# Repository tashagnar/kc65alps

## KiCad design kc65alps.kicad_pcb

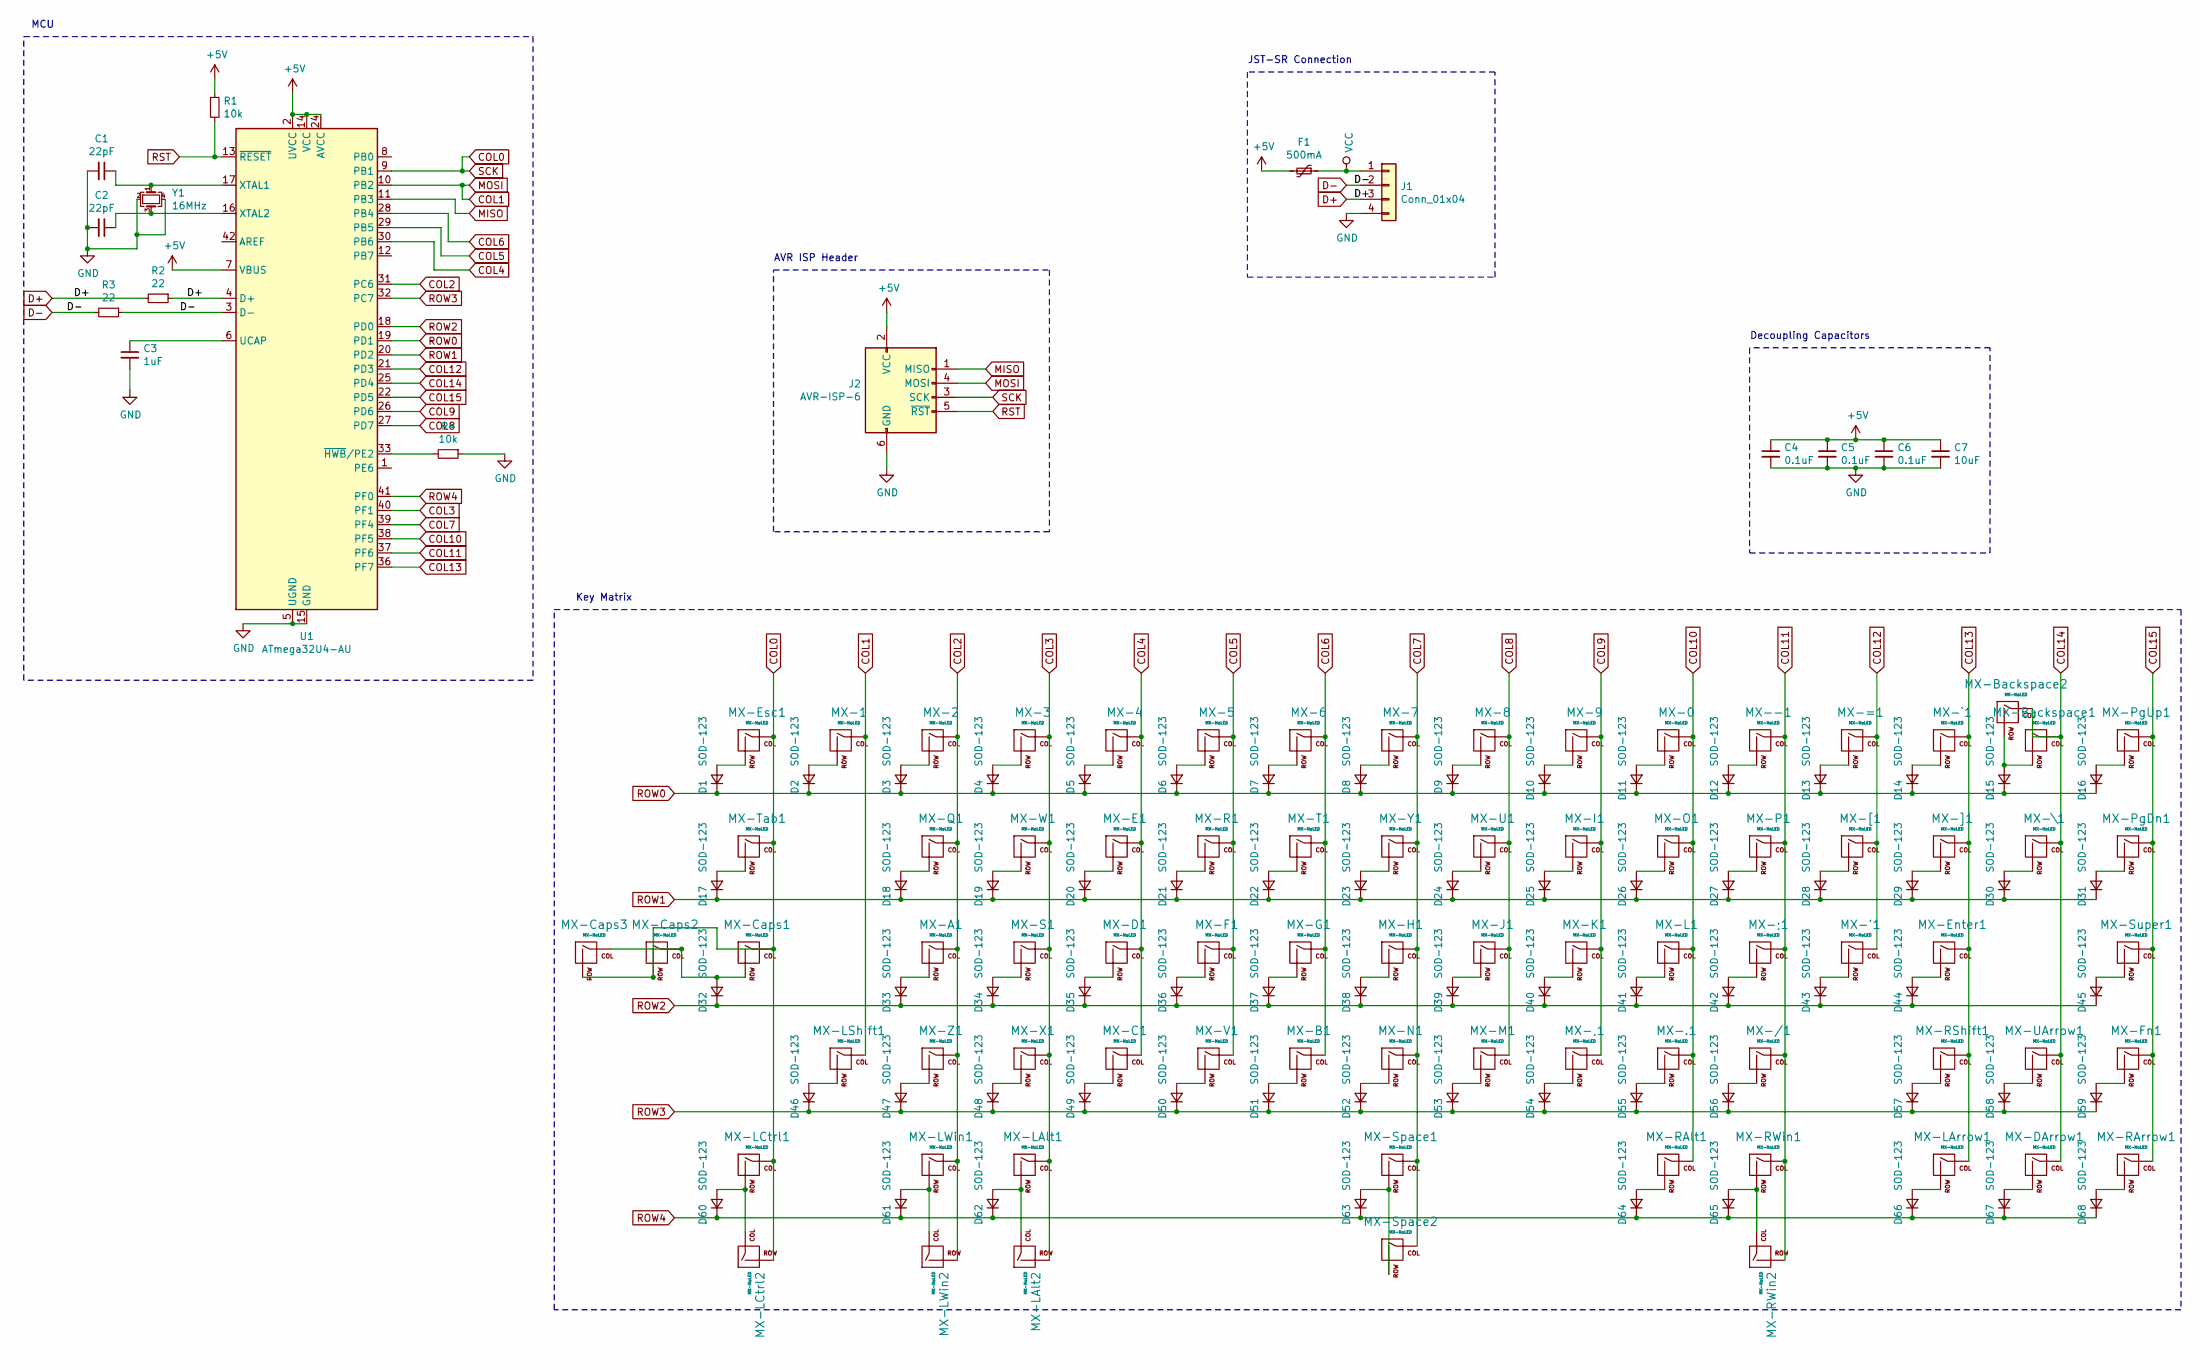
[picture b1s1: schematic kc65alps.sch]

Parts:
C1, C2: 22pF; C_0805
C3: 1uF; C_0805
C4, C5, C6: 0.1uF; C_0805
C7: 10uF; C_0805
D1, D2, D3, D4, D5, D6, D7, D8, D9, D10, D11, D12, D13, D14, D15, D16, D17, D18, D19, D20, D21, D22, D23, D24, D25, D26, D27, D28, D29, D30, D31, D32, D33, D34, D35, D36, D37, D38, D39, D40, D41, D42, D43, D44, D45, D46, D47, D48, D49, D50, D51, D52, D53, D54, D55, D56, D57, D58, D59, D60, D61, D62, D63, D64, D65, D66, D67, D68: SOD-123; D_SOD-123
F1: 500mA; Fuse_SMD1206_Reflow
J1: Conn_01x04; JST-SR-4
J2: AVR-ISP-6; Reset_Pretty-Mask
MX-0, MX-1, MX-2, MX-3, MX-4, MX-5, MX-6, MX-7, MX-8, MX-9, MX-.1: MX-NoLED; ALPS-1U
MX-'1: MX-NoLED; ALPS-1U
MX-,1: MX-NoLED; ALPS-1U
MX--1: MX-NoLED; ALPS-1U
MX-/1: MX-NoLED; ALPS-1U
MX-;1: MX-NoLED; ALPS-1U
MX-=1: MX-NoLED; ALPS-1U
MX-A1: MX-NoLED; ALPS-1U
MX-B1: MX-NoLED; ALPS-1U
MX-Backspace1: MX-NoLED; ALPS-1U
MX-Backspace2: MX-NoLED; ALPS-2U
MX-C1: MX-NoLED; ALPS-1U
MX-Caps1, MX-Caps2, MX-Caps3: MX-NoLED; ALPS-1U
MX-D1: MX-NoLED; ALPS-1U
MX-DArrow1: MX-NoLED; ALPS-1U
MX-E1: MX-NoLED; ALPS-1U
MX-Enter1: MX-NoLED; ALPS-2.25U
MX-Esc1: MX-NoLED; MX-1U-NoLED
MX-F1: MX-NoLED; ALPS-1U
MX-Fn1: MX-NoLED; ALPS-1U
MX-G1: MX-NoLED; ALPS-1U
MX-H1: MX-NoLED; ALPS-1U
MX-I1: MX-NoLED; ALPS-1U
MX-J1: MX-NoLED; ALPS-1U
MX-K1: MX-NoLED; ALPS-1U
MX-L1: MX-NoLED; ALPS-1U
MX-LAlt1: MX-NoLED; ALPS-1.5U
MX-LAlt2: MX-NoLED; ALPS-1.25U
MX-LArrow1: MX-NoLED; ALPS-1U
MX-LCtrl1: MX-NoLED; ALPS-1.5U
MX-LCtrl2: MX-NoLED; ALPS-1.25U
MX-LShift1: MX-NoLED; ALPS-2.25U
MX-LWin1: MX-NoLED; ALPS-1U
MX-LWin2: MX-NoLED; ALPS-1.25U
MX-M1: MX-NoLED; ALPS-1U
MX-N1: MX-NoLED; ALPS-1U
MX-O1: MX-NoLED; ALPS-1U
MX-P1: MX-NoLED; ALPS-1U
MX-PgDn1: MX-NoLED; ALPS-1U
MX-PgUp1: MX-NoLED; ALPS-1U
MX-Q1: MX-NoLED; ALPS-1U
MX-R1: MX-NoLED; ALPS-1U
MX-RAlt1: MX-NoLED; ALPS-1.25U
MX-RArrow1: MX-NoLED; ALPS-1U
MX-RShift1: MX-NoLED; ALPS-1.75U
MX-RWin1: MX-NoLED; ALPS-1.5U
MX-RWin2: MX-NoLED; ALPS-1.25U
MX-S1: MX-NoLED; ALPS-1U
MX-Space1: MX-NoLED; ALPS-7U
MX-Space2: MX-NoLED; ALPS-6.25U
MX-Super1: MX-NoLED; ALPS-1U
MX-T1: MX-NoLED; ALPS-1U
MX-Tab1: MX-NoLED; ALPS-1.5U
MX-U1: MX-NoLED; ALPS-1U
MX-UArrow1: MX-NoLED; ALPS-1U
MX-V1: MX-NoLED; ALPS-1U
MX-W1: MX-NoLED; ALPS-1U
MX-X1: MX-NoLED; ALPS-1U
MX-Y1: MX-NoLED; ALPS-1U
MX-Z1: MX-NoLED; ALPS-1U
MX-[1: MX-NoLED; ALPS-1U
MX-\1: MX-NoLED; ALPS-1.5U
MX-]1: MX-NoLED; ALPS-1U
MX-`1: MX-NoLED; ALPS-1U
R1, R4: 10k; R_0805
R2, R3: 22; R_0805
U1: ATmega32U4-AU; TQFP-44_10x10mm_Pitch0.8mm
Y1: 16MHz; Crystal_SMD_3225-4pin_3.2x2.5mm

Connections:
+5V: C4.1, C5.1, C6.1, C7.1, F1.2, J2.2 (VCC), R1.1, U1.2 (UVCC), U1.7 (VBUS), U1.14 (VCC), U1.24 (AVCC), U1.34 (VCC), U1.44 (AVCC); also elsewhere on the board
COL0: J2.3 (SCK), MX-Caps1.1 (COL), MX-Caps2.2 (ROW), MX-Caps3.2 (ROW), MX-Esc1.1 (COL), MX-LCtrl1.1 (COL), MX-LCtrl2.2 (ROW), MX-Tab1.1 (COL), U1.9 (PB1); also elsewhere on the board
COL1: J2.4 (MOSI), MX-1.1 (COL), MX-LShift1.1 (COL), U1.10 (PB2); also elsewhere on the board
COL2: MX-2.1 (COL), MX-A1.1 (COL), MX-LWin1.1 (COL), MX-LWin2.2 (ROW), MX-Q1.1 (COL), MX-Z1.1 (COL), U1.31 (PC6); also elsewhere on the board
COL3: MX-3.1 (COL), MX-LAlt1.1 (COL), MX-LAlt2.2 (ROW), MX-S1.1 (COL), MX-W1.1 (COL), MX-X1.1 (COL), U1.40 (PF1); also elsewhere on the board
COL4: MX-4.1 (COL), MX-C1.1 (COL), MX-D1.1 (COL), MX-E1.1 (COL), U1.30 (PB6); also elsewhere on the board
COL5: MX-5.1 (COL), MX-F1.1 (COL), MX-R1.1 (COL), MX-V1.1 (COL), U1.29 (PB5); also elsewhere on the board
COL6: MX-6.1 (COL), MX-B1.1 (COL), MX-G1.1 (COL), MX-T1.1 (COL), U1.28 (PB4); also elsewhere on the board
COL7: MX-7.1 (COL), MX-H1.1 (COL), MX-N1.1 (COL), MX-Space1.1 (COL), MX-Space2.1 (COL), MX-Y1.1 (COL), U1.39 (PF4); also elsewhere on the board
COL8: MX-8.1 (COL), MX-J1.1 (COL), MX-M1.1 (COL), MX-U1.1 (COL), U1.27 (PD7); also elsewhere on the board
COL9: MX-9.1 (COL), MX-,1.1 (COL), MX-I1.1 (COL), MX-K1.1 (COL), U1.26 (PD6); also elsewhere on the board
COL10: MX-0.1 (COL), MX-.1.1 (COL), MX-L1.1 (COL), MX-O1.1 (COL), MX-RAlt1.1 (COL), U1.38 (PF5); also elsewhere on the board
COL11: MX--1.1 (COL), MX-/1.1 (COL), MX-;1.1 (COL), MX-P1.1 (COL), MX-RWin1.1 (COL), MX-RWin2.2 (ROW), U1.37 (PF6); also elsewhere on the board
COL12: MX-'1.1 (COL), MX-=1.1 (COL), MX-[1.1 (COL), U1.21 (PD3); also elsewhere on the board
COL13: MX-Enter1.1 (COL), MX-LArrow1.1 (COL), MX-RShift1.1 (COL), MX-]1.1 (COL), MX-`1.1 (COL), U1.36 (PF7); also elsewhere on the board
COL14: MX-Backspace1.1 (COL), MX-Backspace2.1 (COL), MX-DArrow1.1 (COL), MX-UArrow1.1 (COL), MX-\1.1 (COL), U1.25 (PD4); also elsewhere on the board
COL15: MX-Fn1.1 (COL), MX-PgDn1.1 (COL), MX-PgUp1.1 (COL), MX-RArrow1.1 (COL), MX-Super1.1 (COL), U1.22 (PD5); also elsewhere on the board
D+: J1.3, R2.1, R2.2, U1.4 (D+); also elsewhere on the board
D-: J1.2, R3.1, R3.2, U1.3 (D-); also elsewhere on the board
GND: C1.2, C2.2, C3.2, C4.2, C5.2, C6.2, C7.2, J1.4, J2.6 (GND), R4.1, U1.5 (UGND), U1.15 (GND), U1.23 (GND), U1.35 (GND), U1.43 (GND), Y1.2, Y1.4; also elsewhere on the board
MISO: J2.1 (MISO), U1.11 (PB3); also elsewhere on the board
unnamed 21: C1.1, U1.17 (XTAL1), Y1.1; also elsewhere on the board
unnamed 22: C2.1, U1.16 (XTAL2), Y1.3; also elsewhere on the board
unnamed 23: C3.1, U1.6 (UCAP); also elsewhere on the board
unnamed: D1.2 (A), MX-Esc1.2 (ROW)
unnamed: D2.2 (A), MX-1.2 (ROW)
unnamed: D3.2 (A), MX-2.2 (ROW)
unnamed: D4.2 (A), MX-3.2 (ROW)
unnamed: D5.2 (A), MX-4.2 (ROW)
unnamed: D6.2 (A), MX-5.2 (ROW)
unnamed: D7.2 (A), MX-6.2 (ROW)
unnamed: D8.2 (A), MX-7.2 (ROW)
unnamed: D9.2 (A), MX-8.2 (ROW)
unnamed: D10.2 (A), MX-9.2 (ROW)
unnamed: D11.2 (A), MX-0.2 (ROW)
unnamed: D12.2 (A), MX--1.2 (ROW)
unnamed: D13.2 (A), MX-=1.2 (ROW)
unnamed: D14.2 (A), MX-`1.2 (ROW)
unnamed: D15.2 (A), MX-Backspace1.2 (ROW), MX-Backspace2.2 (ROW)
unnamed: D16.2 (A), MX-PgUp1.2 (ROW)
unnamed: D17.2 (A), MX-Tab1.2 (ROW)
unnamed: D18.2 (A), MX-Q1.2 (ROW)
unnamed: D19.2 (A), MX-W1.2 (ROW)
unnamed: D20.2 (A), MX-E1.2 (ROW)
unnamed: D21.2 (A), MX-R1.2 (ROW)
unnamed: D22.2 (A), MX-T1.2 (ROW)
unnamed: D23.2 (A), MX-Y1.2 (ROW)
unnamed: D24.2 (A), MX-U1.2 (ROW)
unnamed: D25.2 (A), MX-I1.2 (ROW)
unnamed: D26.2 (A), MX-O1.2 (ROW)
unnamed: D27.2 (A), MX-P1.2 (ROW)
unnamed: D28.2 (A), MX-[1.2 (ROW)
unnamed: D29.2 (A), MX-]1.2 (ROW)
unnamed: D30.2 (A), MX-\1.2 (ROW)
unnamed: D31.2 (A), MX-PgDn1.2 (ROW)
unnamed: D32.2 (A), MX-Caps1.2 (ROW), MX-Caps2.1 (COL), MX-Caps3.1 (COL)
unnamed: D33.2 (A), MX-A1.2 (ROW)
unnamed: D34.2 (A), MX-S1.2 (ROW)
unnamed: D35.2 (A), MX-D1.2 (ROW)
unnamed: D36.2 (A), MX-F1.2 (ROW)
unnamed: D37.2 (A), MX-G1.2 (ROW)
unnamed: D38.2 (A), MX-H1.2 (ROW)
unnamed: D39.2 (A), MX-J1.2 (ROW)
unnamed: D40.2 (A), MX-K1.2 (ROW)
unnamed: D41.2 (A), MX-L1.2 (ROW)
unnamed: D42.2 (A), MX-;1.2 (ROW)
unnamed: D43.2 (A), MX-'1.2 (ROW)
unnamed: D44.2 (A), MX-Enter1.2 (ROW)
unnamed: D45.2 (A), MX-Super1.2 (ROW)
unnamed: D46.2 (A), MX-LShift1.2 (ROW)
unnamed: D47.2 (A), MX-Z1.2 (ROW)
unnamed: D48.2 (A), MX-X1.2 (ROW)
unnamed: D49.2 (A), MX-C1.2 (ROW)
unnamed: D50.2 (A), MX-V1.2 (ROW)
unnamed: D51.2 (A), MX-B1.2 (ROW)
unnamed: D52.2 (A), MX-N1.2 (ROW)
unnamed: D53.2 (A), MX-M1.2 (ROW)
unnamed: D54.2 (A), MX-,1.2 (ROW)
unnamed: D55.2 (A), MX-.1.2 (ROW)
unnamed: D56.2 (A), MX-/1.2 (ROW)
unnamed: D57.2 (A), MX-RShift1.2 (ROW)
unnamed: D58.2 (A), MX-UArrow1.2 (ROW)
unnamed: D59.2 (A), MX-Fn1.2 (ROW)
unnamed: D60.2 (A), MX-LCtrl1.2 (ROW), MX-LCtrl2.1 (COL)
unnamed: D61.2 (A), MX-LWin1.2 (ROW), MX-LWin2.1 (COL)
unnamed: D62.2 (A), MX-LAlt1.2 (ROW), MX-LAlt2.1 (COL)
unnamed: D63.2 (A), MX-Space1.2 (ROW), MX-Space2.2 (ROW)
unnamed: D64.2 (A), MX-RAlt1.2 (ROW)
unnamed: D65.2 (A), MX-RWin1.2 (ROW), MX-RWin2.1 (COL)
unnamed: D66.2 (A), MX-LArrow1.2 (ROW)
unnamed: D67.2 (A), MX-DArrow1.2 (ROW)
unnamed: D68.2 (A), MX-RArrow1.2 (ROW)
unnamed 92: R4.2, U1.33 (~HWB~/PE2); also elsewhere on the board
ROW0: D1.1 (K), D2.1 (K), D3.1 (K), D4.1 (K), D5.1 (K), D6.1 (K), D7.1 (K), D8.1 (K), D9.1 (K), D10.1 (K), D11.1 (K), D12.1 (K), D13.1 (K), D14.1 (K), D15.1 (K), D16.1 (K), U1.19 (PD1); also elsewhere on the board
ROW1: D17.1 (K), D18.1 (K), D19.1 (K), D20.1 (K), D21.1 (K), D22.1 (K), D23.1 (K), D24.1 (K), D25.1 (K), D26.1 (K), D27.1 (K), D28.1 (K), D29.1 (K), D30.1 (K), D31.1 (K), U1.20 (PD2); also elsewhere on the board
ROW2: D32.1 (K), D33.1 (K), D34.1 (K), D35.1 (K), D36.1 (K), D37.1 (K), D38.1 (K), D39.1 (K), D40.1 (K), D41.1 (K), D42.1 (K), D43.1 (K), D44.1 (K), D45.1 (K), U1.18 (PD0); also elsewhere on the board
ROW3: D46.1 (K), D47.1 (K), D48.1 (K), D49.1 (K), D50.1 (K), D51.1 (K), D52.1 (K), D53.1 (K), D54.1 (K), D55.1 (K), D56.1 (K), D57.1 (K), D58.1 (K), D59.1 (K), U1.32 (PC7); also elsewhere on the board
ROW4: D60.1 (K), D61.1 (K), D62.1 (K), D63.1 (K), D64.1 (K), D65.1 (K), D66.1 (K), D67.1 (K), D68.1 (K), U1.41 (PF0); also elsewhere on the board
RST: J2.5 (~RST), R1.2, U1.13 (~RESET); also elsewhere on the board
VCC: F1.1, J1.1

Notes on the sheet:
MCU
AVR ISP Header
JST-SR Connection
Decoupling Capacitors
Key Matrix

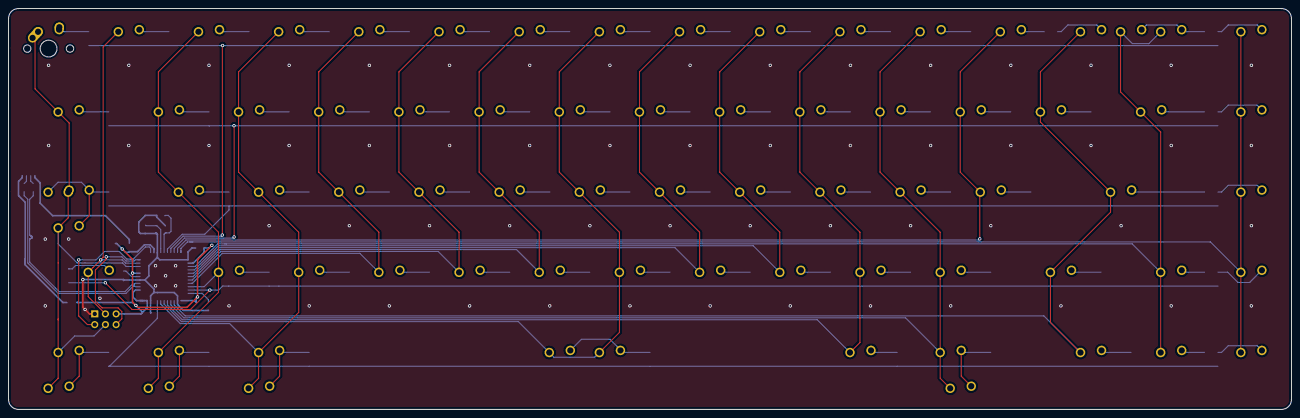
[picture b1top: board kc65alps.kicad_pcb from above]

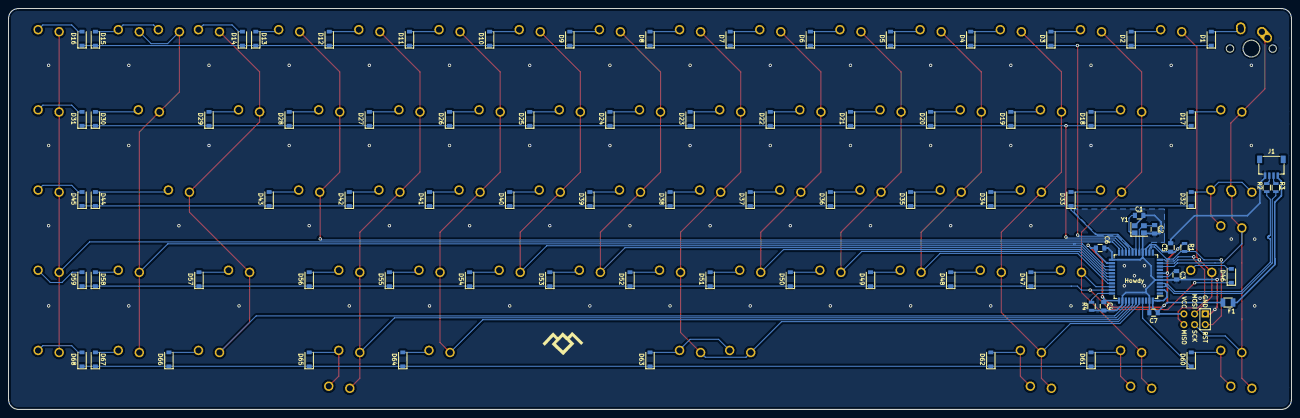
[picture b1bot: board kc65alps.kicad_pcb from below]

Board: 2 copper layers, 304.8 x 95.3 mm, 160 parts (84 on the bottom side), 100 nets.

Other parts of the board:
Howdy: ATmega32U4-AU; TQFP-44_10x10mm_Pitch0.8mm

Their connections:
+5V: Howdy.2, Howdy.7, Howdy.14, Howdy.24, Howdy.34, Howdy.44; also elsewhere on the board
COL0: Howdy.9; also elsewhere on the board
COL1: Howdy.10; also elsewhere on the board
COL2: Howdy.31; also elsewhere on the board
COL3: Howdy.40; also elsewhere on the board
COL4: Howdy.30; also elsewhere on the board
COL5: Howdy.29; also elsewhere on the board
COL6: Howdy.28; also elsewhere on the board
COL7: Howdy.39; also elsewhere on the board
COL8: Howdy.27; also elsewhere on the board
COL9: Howdy.26; also elsewhere on the board
COL10: Howdy.38; also elsewhere on the board
COL11: Howdy.37; also elsewhere on the board
COL12: Howdy.21; also elsewhere on the board
COL13: Howdy.36; also elsewhere on the board
COL14: Howdy.25; also elsewhere on the board
COL15: Howdy.22; also elsewhere on the board
D+: Howdy.4; also elsewhere on the board
D-: Howdy.3; also elsewhere on the board
GND: Howdy.5, Howdy.15, Howdy.23, Howdy.35, Howdy.43; also elsewhere on the board
MISO: Howdy.11; also elsewhere on the board
unnamed 21: Howdy.17; also elsewhere on the board
unnamed 22: Howdy.16; also elsewhere on the board
unnamed 23: Howdy.6; also elsewhere on the board
unnamed 92: Howdy.33; also elsewhere on the board
ROW0: Howdy.19; also elsewhere on the board
ROW1: Howdy.20; also elsewhere on the board
ROW2: Howdy.18; also elsewhere on the board
ROW3: Howdy.32; also elsewhere on the board
ROW4: Howdy.41; also elsewhere on the board
RST: Howdy.13; also elsewhere on the board

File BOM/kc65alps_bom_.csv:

Component,Description,Part,References,Value,Footprint,Quantity Per PCB,Datasheet
1,"Unpolarized capacitor, small symbol",C_Small,C4 C5 C6,0.1uF,C_0805,3,~
2,"Unpolarized capacitor, small symbol",C_Small,C7,10uF,C_0805,1,~
3,"Unpolarized capacitor, small symbol",C_Small,C3,1uF,C_0805,1,~
4,"Unpolarized capacitor, small symbol",C_Small,C1 C2,22pF,C_0805,2,~
5,"Diode, small symbol",D_Small,D1 D2 D3 D4 D5 D6 D7 D8 D9 D10 D11 D12 D13 D14 D15 D16 D17 D18 D19 D20 D21 D22 D23 D24 D25 D26 D27 D28 D29 D30 D31 D32 D33 D34 D35 D36 D37 D38 D39 D40 D41 D42 D43 D44 D45 D46 D47 D48 D49 D50 D51 D52 D53 D54 D55 D56 D57 D58 D59 D60 D61 D62 D63 D64 D65 D66 D67 D68,SOD-123,D_SOD-123,68,~
6,"Resettable fuse, polymeric positive temperature coefficient, small symbol",Polyfuse_Small,F1,500mA,Fuse_SMD1206_Reflow,1,~
7,Atmel 6-pin ISP connector,AVR-ISP-6,J2,AVR-ISP-6,Reset_Pretty-Mask,1, ~
8,"Generic connector, single row, 01x04, script generated (kicad-library-utils/schlib/autogen/connector/)",Conn_01x04,J1,Conn_01x04,JST-SR-4,1,~
9,,MX-NoLED,"MX-0 MX-1 MX-2 MX-3 MX-4 MX-5 MX-6 MX-7 MX-8 MX-9 MX-'1 MX-,1 MX--1 MX-.1 MX-/1 MX-;1 MX-=1 MX-A1 MX-B1 MX-Backspace1 MX-C1 MX-Caps1 MX-Caps2 MX-Caps3 MX-D1 MX-DArrow1 MX-E1 MX-F1 MX-Fn1 MX-G1 MX-H1 MX-I1 MX-J1 MX-K1 MX-L1 MX-LArrow1 MX-LWin1 MX-M1 MX-N1 MX-O1 MX-P1 MX-PgDn1 MX-PgUp1 MX-Q1 MX-R1 MX-RArrow1 MX-S1 MX-Super1 MX-T1 MX-U1 MX-UArrow1 MX-V1 MX-W1 MX-X1 MX-Y1 MX-Z1 MX-[1 MX-]1 MX-`1",MX-NoLED,ALPS-1U,59,
10,,MX-NoLED,MX-Backspace2,MX-NoLED,ALPS-2U,1,
11,,MX-NoLED,MX-Enter1 MX-LShift1,MX-NoLED,ALPS-2.25U,2,
12,,MX-NoLED,MX-Esc1,MX-NoLED,MX-1U-NoLED,1,
13,,MX-NoLED,MX-LAlt1 MX-LCtrl1 MX-RWin1 MX-Tab1 MX-\1,MX-NoLED,ALPS-1.5U,5,
14,,MX-NoLED,MX-LAlt2 MX-LCtrl2 MX-LWin2 MX-RAlt1 MX-RWin2,MX-NoLED,ALPS-1.25U,5,
15,,MX-NoLED,MX-RShift1,MX-NoLED,ALPS-1.75U,1,
16,,MX-NoLED,MX-Space1,MX-NoLED,ALPS-7U,1,
17,,MX-NoLED,MX-Space2,MX-NoLED,ALPS-6.25U,1,
18,"Resistor, small symbol",R_Small,R1 R4,10k,R_0805,2,~
19,"Resistor, small symbol",R_Small,R2 R3,22,R_0805,2,~
20,"16MHz, 32kB Flash, 2.5kB SRAM, 1kB EEPROM, USB 2.0, TQFP-44",ATmega32U4-AU,U1,ATmega32U4-AU,TQFP-44_10x10mm_Pitch0.8mm,1,http://ww1.microchip.com/downloads/en/DeviceDoc/Atmel-7766-8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
21,"Four pin crystal, GND on pins 2 and 4, small symbol",Crystal_GND24_Small,Y1,16MHz,Crystal_SMD_3225-4pin_3.2x2.5mm,1,~





Component Groups:,21
Component Count:,160
Fitted Components:,160
Number of PCBs:,1
Total components:,160
Schematic Version:,
Schematic Date:,
PCB Variant:,default
BoM Date:,1/9/2020 6:19:34 PM
Schematic Source:,D:\GitHub\kc65alps\kc65alps.sch
KiCad Version:,Eeschema (5.1.4)-1

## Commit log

2019-12-16 Initialize Project
2019-12-16 Add submodules
2019-12-16 Add footprint libraries
2019-12-16 Schematic update
2019-12-17 Updating Schematic
2019-12-18 PCB update
2019-12-18 Update Schematic
2020-01-09 Create gerbers
2020-01-10 Generate Bom
